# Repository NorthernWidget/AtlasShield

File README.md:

AtlasShield
===========

Arduino shield (expansion board) to interface with Atlas scientific boards and sensors

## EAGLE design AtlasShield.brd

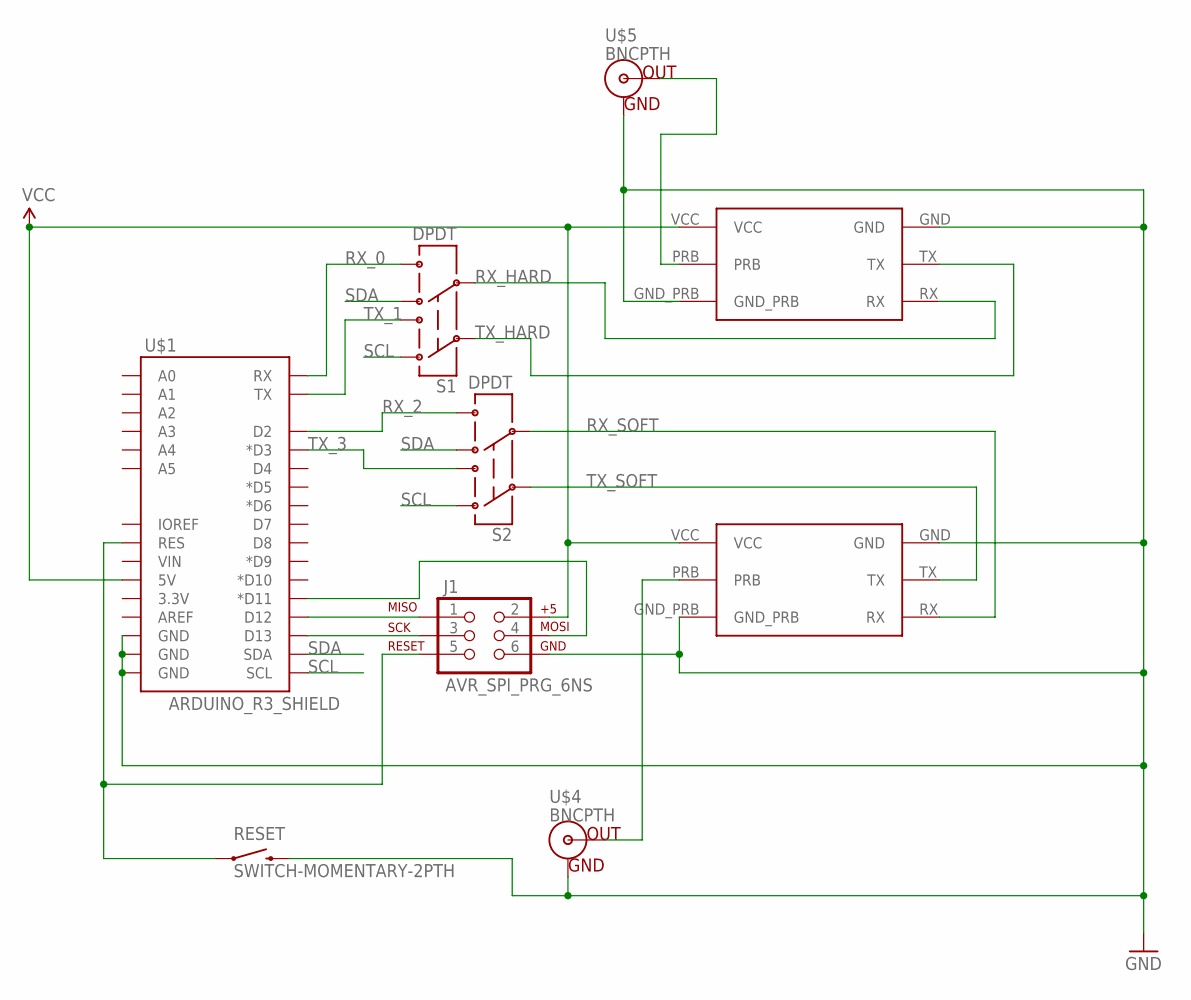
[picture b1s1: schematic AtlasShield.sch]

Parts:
J1: AVR_SPI_PRG_6NS; 2X3-NS
RESET: SWITCH-MOMENTARY-2PTH; TACTILE-PTH
S1, S2: DPDT; AYZ0202
U$1: ARDUINO_R3_SHIELD; UNO_R3_SHIELD
U$2, U$3: ATLAS-CIRCUIT
U$4, U$5: BNCPTH; BNC

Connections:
GND: J1.6, RESET.3 (2), U$1.GND@0 (GND), U$1.GND@1 (GND), U$1.GND@2 (GND), U$2.GND, U$2.GND_PRB, U$3.GND, U$3.GND_PRB, U$4.GND, U$5.GND
unnamed: J1.5, RESET.1, U$1.RES
unnamed: J1.4, U$1.D11 (*D11)
unnamed: J1.1, U$1.D12
unnamed: J1.3, U$1.D13
unnamed: U$2.PRB, U$5.S (OUT)
unnamed: U$3.PRB, U$4.S (OUT)
RX_0: S1.6, U$1.RX
RX_2: S2.6, U$1.D2
RX_HARD: S1.5, U$2.RX
RX_SOFT: S2.5, U$3.RX
SCL: S1.1, S2.1, U$1.SCL
SDA: S1.4, S2.4, U$1.SDA
TX_1: S1.3, U$1.TX
TX_3: S2.3, U$1.D3 (*D3)
TX_HARD: S1.2, U$2.TX
TX_SOFT: S2.2, U$3.TX
VCC: J1.2, U$1.5V, U$2.VCC, U$3.VCC

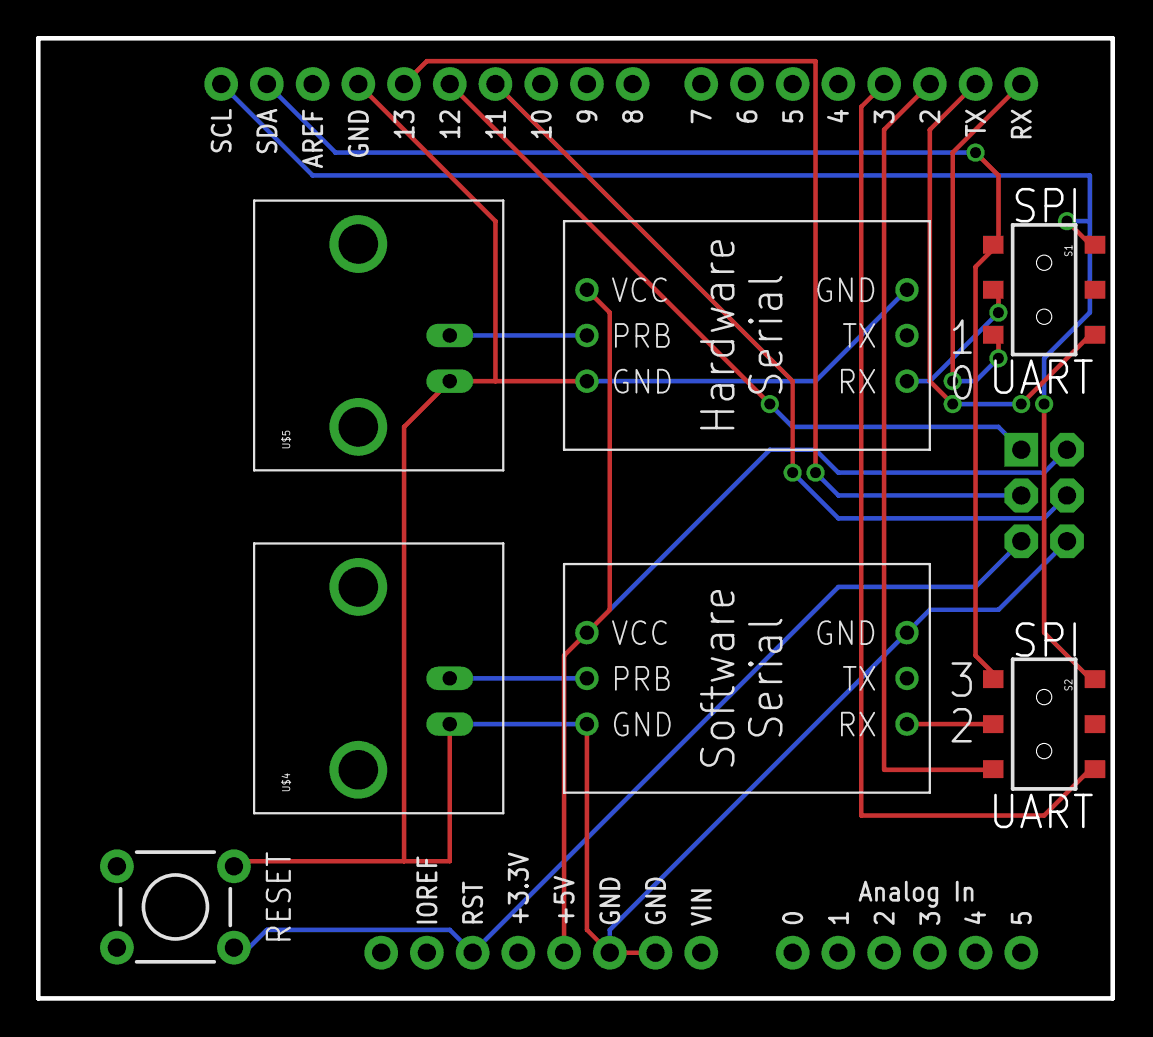
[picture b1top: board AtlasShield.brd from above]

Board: 2 copper layers, 59.8 x 53.3 mm, 9 parts (0 on the bottom side), 18 nets.

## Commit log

2014-06-26 Create LICENSE.md
    CC-BY-SA 4.0
2014-06-27 gitignore from ALog-LogMega
2014-06-27 Initial draft of 2x UART Arduino shield for Atlas Scientific sensors and their circuits
2014-06-27 added DPDT switches to optionally send either sensor to the SPI bus

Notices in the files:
parts and their libraries:
SparkFun-Boards: Licensing: CC v3.0 Share-Alike You are welcome to use this library for commercial purposes.
